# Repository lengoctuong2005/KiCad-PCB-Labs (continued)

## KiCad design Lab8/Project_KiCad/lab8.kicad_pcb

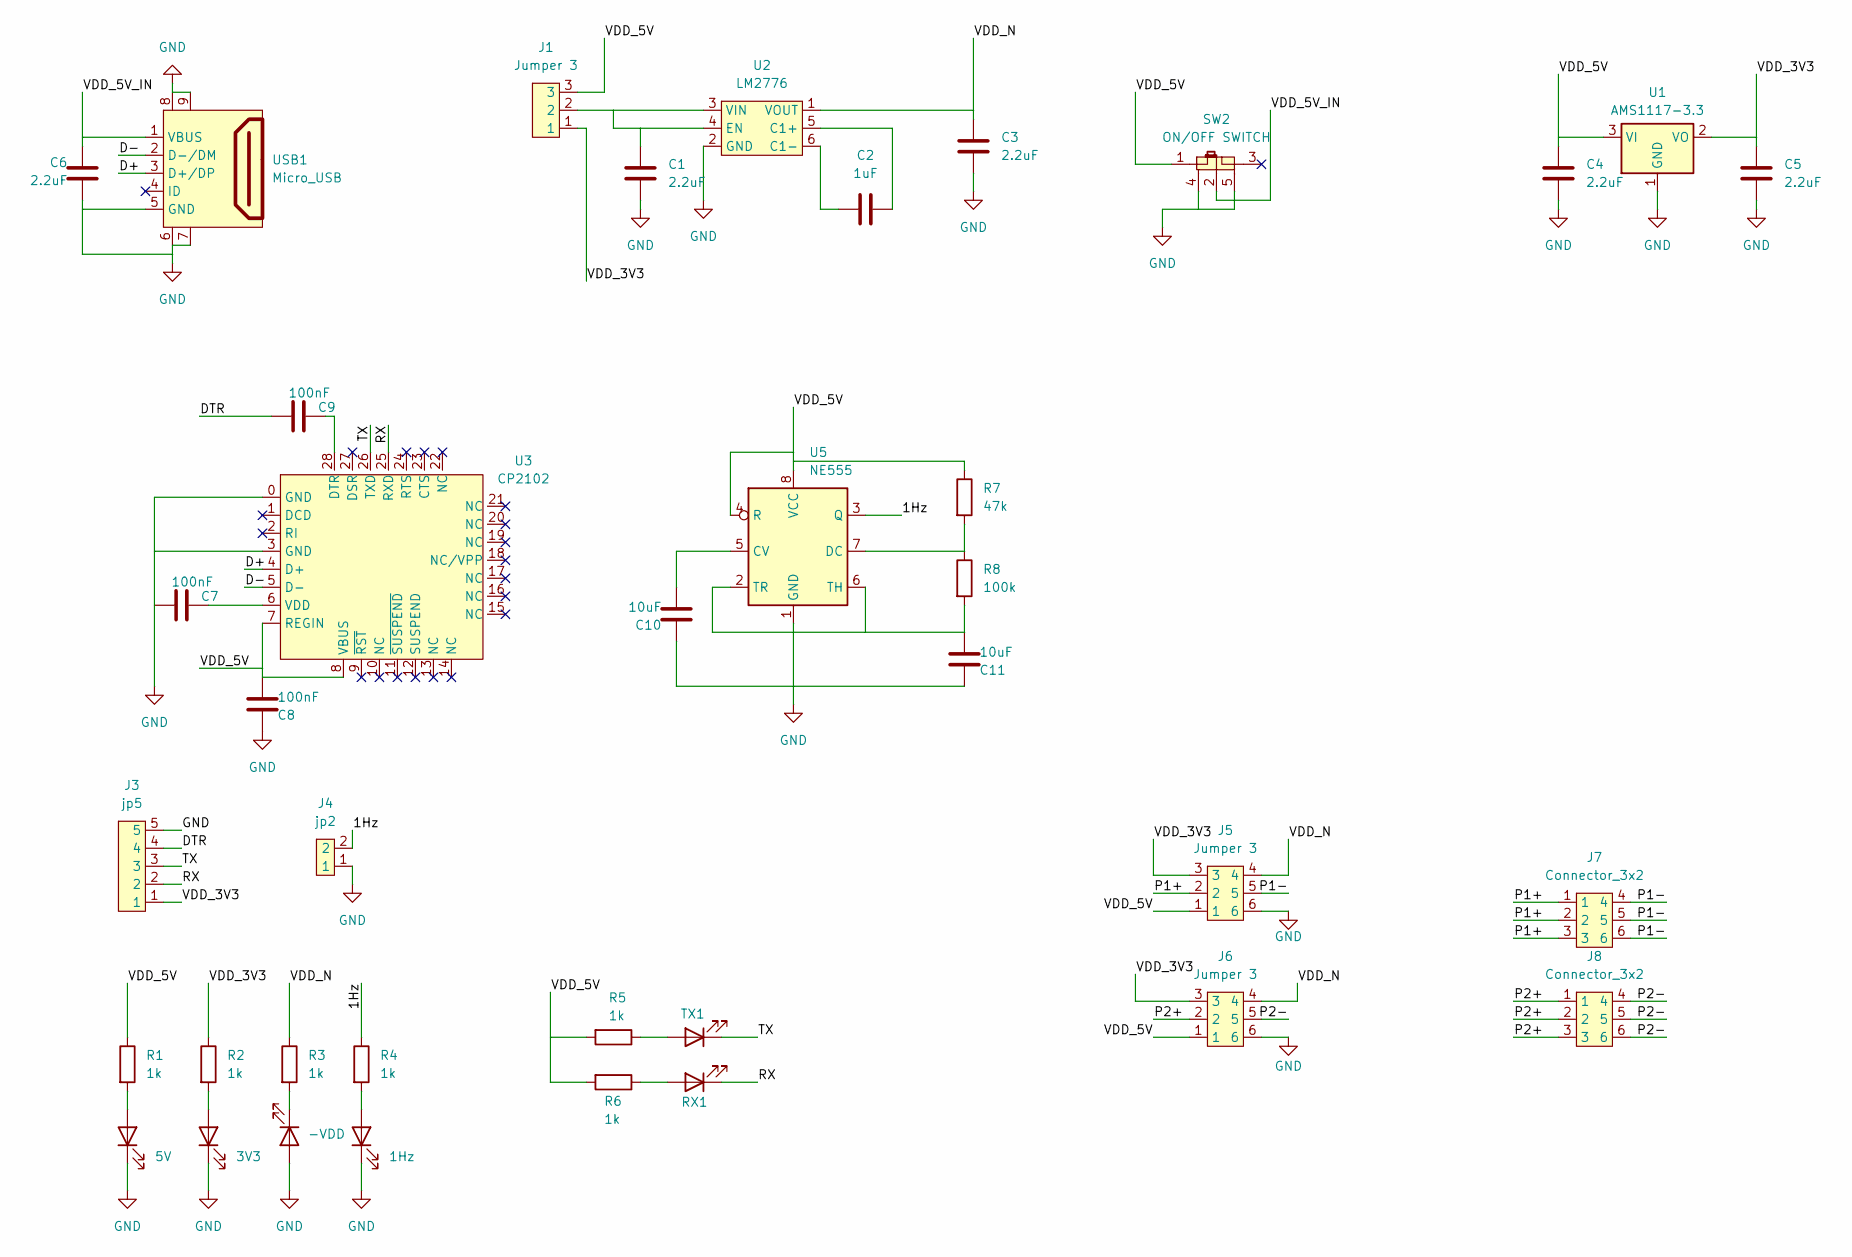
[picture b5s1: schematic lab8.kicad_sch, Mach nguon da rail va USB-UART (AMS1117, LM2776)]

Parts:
C1, C3, C4, C5, C6: 2.2uF; C_0805_2012Metric
C2: 1uF; C_0805_2012Metric
C7, C8, C9: 100nF; C_0805_2012Metric
C10, C11: 10uF; CP_Radial_D5.0mm_P2.50mm
D1: 5V; LED_0805_2012Metric
D2: 3V3; LED_0805_2012Metric
D3: -VDD; LED_0805_2012Metric
D4: 1Hz; LED_0805_2012Metric
D5: RX1; LED_0805_2012Metric
D6: TX1; LED_0805_2012Metric
J1: Jumper 3; PinHeader_1x03_P2.54mm_Vertical
J3: jp5; PinHeader_1x05_P2.54mm_Vertical
J4: jp2; PinHeader_1x02_P2.54mm_Vertical
J5, J6: Jumper 3
J7, J8: Connector_3x2; Connector 3x2
R1, R2, R3, R4, R5, R6: 1k; R_0805_2012Metric
R7: 47k; R_0805_2012Metric
R8: 100k; R_0805_2012Metric
SW2: ON/OFF SWITCH; SWITCH_ON_OFF
U1: AMS1117-3.3; SOT-223-3_TabPin2
U2: LM2776; SOT-23-6
U3: CP2102
U5: NE555; SO-8_3.9x4.9mm_P1.27mm
USB1: Micro_USB

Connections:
/1Hz: J4.2, R4.1, U5.3 (Q)
/D+: U3.4 (D+), USB1.3 (D+/DP)
/D-: U3.5 (D-), USB1.2 (D-/DM)
/DTR: C9.1, J3.4
/P1+: J5.2, J7.1, J7.2, J7.3
/P1-: J5.5, J7.4, J7.5, J7.6
/P2+: J6.2, J8.1, J8.2, J8.3
/P2-: J6.5, J8.4, J8.5, J8.6
/RX: D5.1 (K), J3.2, U3.25 (RXD)
/TX: D6.1 (K), J3.3, U3.26 (TXD)
/VDD_3V3: C5.1, J1.1, J3.1, J5.3, J6.3, R2.1, U1.2 (VO)
/VDD_5V: C4.1, C8.2, J1.3, J5.1, J6.1, R1.1, R5.2, R6.2, R7.1, SW2.1, U1.3 (VI), U3.7 (REGIN), U3.8 (VBUS), U5.4 (R), U5.8 (VCC)
/VDD_5V_IN: C6.1, SW2.2, USB1.1 (VBUS)
/VDD_N: C3.1, J5.4, J6.4, R3.1, U2.1 (VOUT)
GND: C1.2, C3.2, C4.2, C5.2, C6.2, C7.1, C8.1, C10.1, C11.1, D1.1 (K), D2.1 (K), D3.2 (A), D4.1 (K), J3.5, J4.1, J5.6, J6.6, SW2.4, SW2.5, U1.1 (GND), U2.2 (GND), U3.0 (GND), U3.3 (GND), U5.1 (GND), USB1.5 (GND), USB1.6, USB1.7, USB1.8, USB1.9
unnamed: D1.2 (A), R1.2
unnamed: D2.2 (A), R2.2
unnamed: D3.1 (K), R3.2
unnamed: D4.2 (A), R4.2
unnamed: D5.2 (A), R6.1
unnamed: D6.2 (A), R5.1
unnamed: C2.2, U2.5 (C1+)
unnamed: C2.1, U2.6 (C1-)
unnamed: C1.1, J1.2, U2.3 (VIN), U2.4 (EN)
unnamed: C9.2, U3.28 (DTR)
unnamed: C7.2, U3.6 (VDD)
unnamed: C10.2, U5.5 (CV)
unnamed: R7.2, R8.1, U5.7 (DC)
unnamed: C11.2, R8.2, U5.2 (TR), U5.6 (TH)

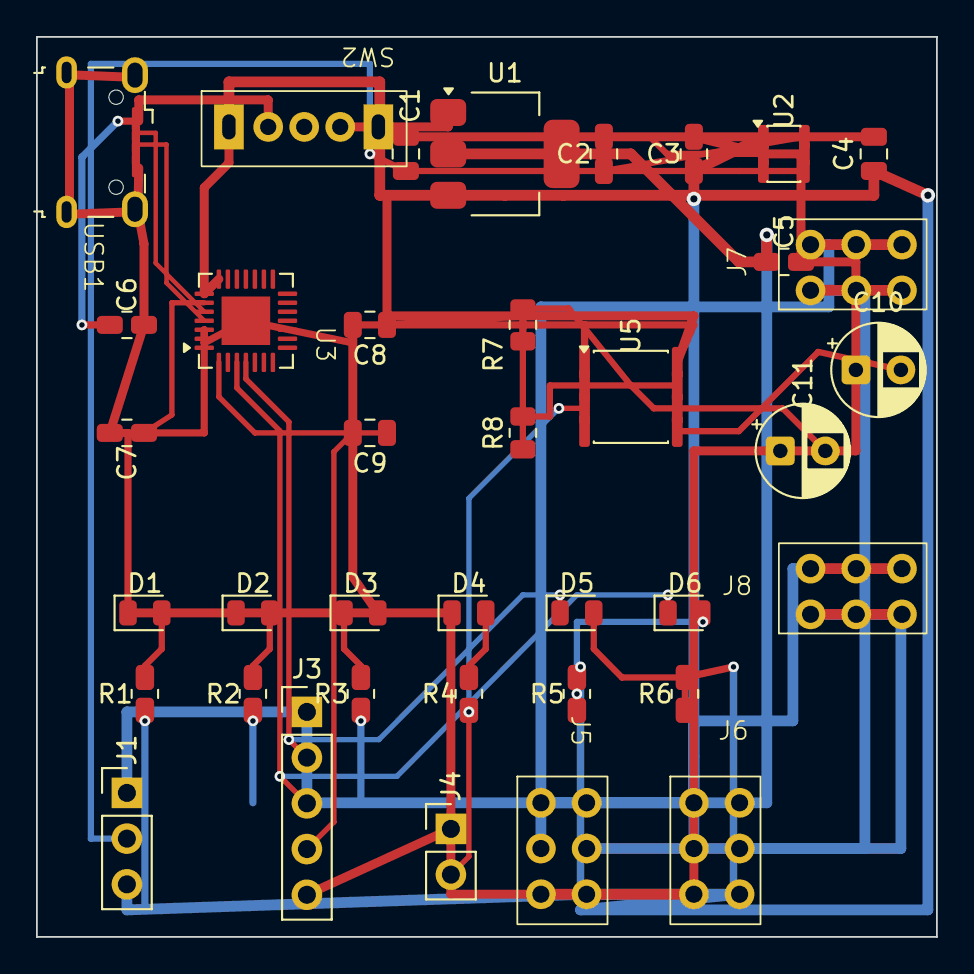
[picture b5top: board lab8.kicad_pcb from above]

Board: 2 copper layers, 50.0 x 50.0 mm, 38 parts (0 on the bottom side), 29 nets.

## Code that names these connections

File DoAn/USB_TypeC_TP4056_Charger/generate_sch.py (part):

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			)
			(symbol "TP4056_1_1"
				(pin input line (at -10.16 2.54 0) (length 2.54) (name "TEMP" (effects (font (size 1.27 1.27)))) (number "1" (effects (font (size 1.27 1.27)))))
				(pin input line (at -10.16 0 0) (length 2.54) (name "PROG" (effects (font (size 1.27 1.27)))) (number "2" (effects (font (size 1.27 1.27)))))
				(pin power_in line (at 0 -10.16 90) (length 2.54) (name "GND" (effects (font (size 1.27 1.27)))) (number "3" (effects (font (size 1.27 1.27)))))
				(pin power_in line (at -10.16 -2.54 0) (length 2.54) (name "VCC" (effects (font (size 1.27 1.27)))) (number "4" (effects (font (size 1.27 1.27)))))
				(pin power_out line (at 10.16 2.54 180) (length 2.54) (name "BAT" (effects (font (size 1.27 1.27)))) (number "5" (effects (font (size 1.27 1.27)))))
				(pin open_collector line (at 10.16 0 180) (length 2.54) (name "~{{STDBY}}" (effects (font (size 1.27 1.27)))) (number "6" (effects (font (size 1.27 1.27)))))
				(pin open_collector line (at 10.16 -2.54 180) (length 2.54) (name "~{{CHRG}}" (effects (font (size 1.27 1.27)))) (number "7" (effects (font (size 1.27 1.27)))))
				(pin input line (at -10.16 -5.08 0) (length 2.54) (name "CE" (effects (font (size 1.27 1.27)))) (number "8" (effects (font (size 1.27 1.27)))))
				(pin power_in line (at 2.54 -10.16 90) (length 2.54) (name "EP" (effects (font (size 1.27 1.27)))) (number "9" (effects (font (size 1.27 1.27)))))
			)
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out += pwr("GND", ux, uy+10.16) + "\n"
out += pwr("GND", ux-2.54, uy+10.16) + "\n"

out += global_label("BAT_OUT", ux+10.16, uy-2.54, 0) + "\n"
out += global_label("STDBY", ux+10.16, uy, 0) + "\n"
out += global_label("CHRG", ux+10.16, uy+2.54, 0) + "\n"

# Decoupling Caps
out += global_label("VBUS", 111.76, 60.96, 180) + "\n"
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out += w(157.48, 73.66, 157.48, 76.2) + "\n"
out += p("D1", "Device:LED", "D1", "RED", 157.48, 80.01, 270, "LED_SMD:LED_0805_2012Metric") + "\n"
out += w(157.48, 83.82, 157.48, 86.36) + "\n"
out += global_label("CHRG", 157.48, 86.36, 270) + "\n"

out += w(157.48, 60.96, 167.64, 60.96) + "\n"
out += w(167.64, 60.96, 167.64, 66.04) + "\n"
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out += w(167.64, 73.66, 167.64, 76.2) + "\n"
out += p("D2", "Device:LED", "D2", "GREEN", 167.64, 80.01, 270, "LED_SMD:LED_0805_2012Metric") + "\n"
out += w(167.64, 83.82, 167.64, 86.36) + "\n"
out += global_label("STDBY", 167.64, 86.36, 270) + "\n"

# Protection Circuit
dwx, dwy = 182.88, 132.08
out += p("U2", "charger:DW01A", "U2", "DW01A", dwx, dwy, 0, "charger:SOT-23-6") + "\n"
out += global_label("DW_OD", dwx+10.16, dwy-1.27, 0) + "\n"
out += global_label("DW_OC", dwx+10.16, dwy+1.27, 0) + "\n"

out += w(dwx, dwy-8.89, dwx, dwy-15.24) + "\n"
out += p("R6", "Device:R_US", "R6", "100", dwx, dwy-19.05, 90, "Resistor_SMD:R_0805_2012Metric") + "\n"
out += w(dwx, dwy-22.86, dwx, dwy-25.4) + "\n"
out += global_label("BAT_OUT", dwx, dwy-25.4, 270) + "\n"

out += w(dwx, dwy-15.24, dwx+10.16, dwy-15.24) + "\n"
out += w(dwx+10.16, dwy-15.24, dwx+10.16, dwy-10.16) + "\n"
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out += pwr("GND", dwx+10.16, dwy+10.16) + "\n"

out += w(dwx, dwy+6.35, dwx, dwy+15.24) + "\n"
out += global_label("BAT_MINUS", dwx, dwy+15.24, 90) + "\n"

out += w(dwx-10.16, dwy-3.81, dwx-15.24, dwy-3.81) + "\n"
out += p("R7", "Device:R_US", "R7", "1k", dwx-19.05, dwy-3.81, 270, "Resistor_SMD:R_0805_2012Metric") + "\n"
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
fsx, fsy = 233.68, 132.08
out += p("Q1", "charger:FS8205A", "Q1", "FS8205A", fsx, fsy, 0, "charger:TSSOP-8_4.4x3mm_P0.65mm") + "\n"
out += global_label("DW_OD", fsx-7.62, fsy-3.81, 180) + "\n"
out += global_label("DW_OC", fsx-7.62, fsy-1.27, 180) + "\n"

out += w(fsx+7.62, fsy-3.81, fsx+15.24, fsy-3.81) + "\n"
out += pwr("GND", fsx+15.24, fsy-3.81) + "\n"

out += w(fsx+7.62, fsy-1.27, fsx+15.24, fsy-1.27) + "\n"
out += global_label("BAT_MINUS", fsx+15.24, fsy-1.27, 0) + "\n"
out += no_conn(fsx-7.62, fsy+1.27) + "\n"

# Battery Connector
bx, by = 264.16, 132.08
out += p("J2", "Connector_Generic:Conn_01x02", "J2", "BATT", bx, by, 0, "charger:JST_PH_B2B-PH-SM4-TB") + "\n"
out += w(bx-5.08, by, bx-15.24, by) + "\n"
out += global_label("BAT_OUT", bx-15.24, by, 180) + "\n"

out += w(bx-5.08, by+2.54, bx-15.24, by+2.54) + "\n"
out += global_label("BAT_MINUS", bx-15.24, by+2.54, 180) + "\n"

# BAT_OUT decouple
out += global_label("BAT_OUT", 182.88, 60.96, 180) + "\n"
out += w(182.88, 60.96, 187.96, 60.96) + "\n"
out += w(187.96, 60.96, 187.96, 66.04) + "\n"
out += p("C3", "Device:C", "C3", "10uF", 187.96, 69.85, 0, "Capacitor_SMD:C_0805_2012Metric") + "\n"
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out += pwr("PWR_FLAG", 132.08, 45.72) + "\n"

out += w(142.24, 40.64, 142.24, 45.72) + "\n"
out += global_label("BAT_OUT", 142.24, 40.64, 270) + "\n"
out += pwr("PWR_FLAG", 142.24, 45.72) + "\n"

out += w(152.4, 40.64, 152.4, 45.72) + "\n"
out += global_label("BAT_MINUS", 152.4, 40.64, 270) + "\n"
out += pwr("PWR_FLAG", 152.4, 45.72) + "\n"

out += ")"
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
